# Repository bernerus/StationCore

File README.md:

View this project on [CADLAB.io](https://cadlab.io/project/27342). 

# StationCore

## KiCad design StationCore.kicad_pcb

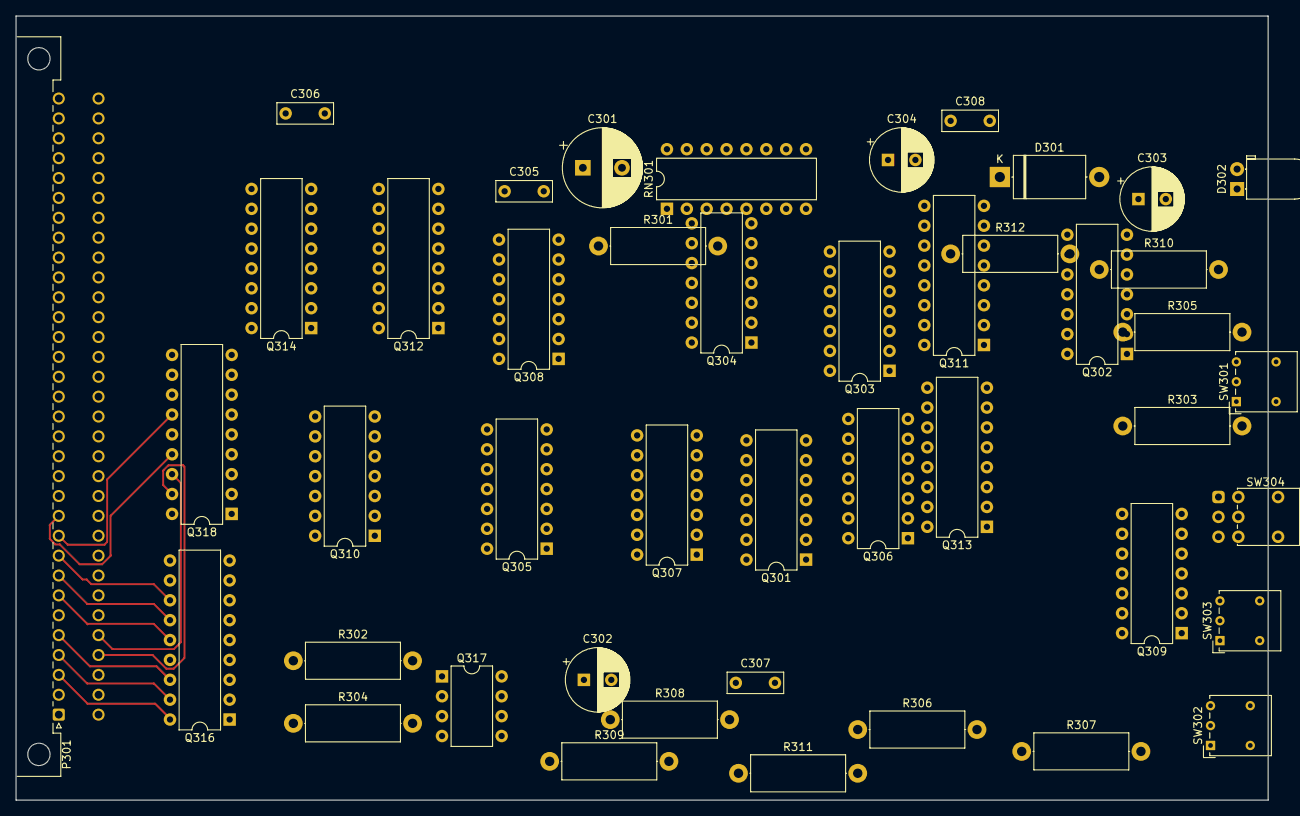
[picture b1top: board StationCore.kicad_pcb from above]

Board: 2 copper layers, 160.0 x 100.2 mm, 45 parts (0 on the bottom side), 69 nets.

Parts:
C301: 100μF; CP_Radial_D10.0mm_P5.00mm
C302: 10μF; CP_Radial_D8.0mm_P3.50mm
C303: 39μF; CP_Radial_D8.0mm_P3.50mm
C304: 22μF; CP_Radial_D8.0mm_P3.50mm
C305, C306, C307, C308: 47n; C_Rect_L7.0mm_W2.5mm_P5.00mm
D301: BZX74C4v2; D_DO-201AE_P12.70mm_Horizontal
D302: PA RDY; LED_D5.0mm_Horizontal_O1.27mm_Z3.0mm
P301: DIN2; DIN41612_C_2x32_Male_Horizontal_THT
Q301: 7402; DIP-14_W7.62mm
Q302: 74LS32; DIP-14_W7.62mm
Q303, Q309: 74LS08; DIP-14_W7.62mm
Q304: 74HCT04; DIP-14_W7.62mm
Q305: 74HC74; DIP-14_W7.62mm
Q306, Q307: 74LS00; DIP-14_W7.62mm
Q308: 74HC14; DIP-14_W7.62mm
Q310: 74LS21; DIP-14_W7.62mm
Q311, Q313: 74LS123; DIP-16_W7.62mm
Q312, Q314: PCF8574; DIP-16_W7.62mm
Q316, Q318: ULN2803A; DIP-18_W7.62mm
Q317: 82B715; DIP-8_W7.62mm
R301: 470k; R_Axial_DIN0414_L11.9mm_D4.5mm_P15.24mm_Horizontal
R302, R303: 39k; R_Axial_DIN0414_L11.9mm_D4.5mm_P15.24mm_Horizontal
R304, R305, R306: 22k; R_Axial_DIN0414_L11.9mm_D4.5mm_P15.24mm_Horizontal
R307, R311, R312: 27k; R_Axial_DIN0414_L11.9mm_D4.5mm_P15.24mm_Horizontal
R308, R309: 680; R_Axial_DIN0414_L11.9mm_D4.5mm_P15.24mm_Horizontal
R310: 279; R_Axial_DIN0414_L11.9mm_D4.5mm_P15.24mm_Horizontal
RN301: 4k7; DIP-16_W7.62mm
SW301: XRX_432; SW_Lever_1P2T_NKK_GW12LxH
SW302: QRO; SW_Lever_1P2T_NKK_GW12LxH
SW303: xxx; SW_Lever_1P2T_NKK_GW12LxH
SW304: PA_OFF; SW_Push_2P2T_Vertical_E-Switch_800UDP8P1A1M6

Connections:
432_L: P301.a6, Q301.6, Q304.1, Q305.3 (C), Q306.13, Q307.5, Q312.12 (P7), RN301.8 (R8)
432_RX: Q309.6, Q316.4 (I4)
432_RX_PWR_EN: Q301.13, Q316.3 (I3)
432_RX_PWR_EN_L: P301.a5, Q316.16 (O3)
432_TX_PWR_EN: Q301.3, Q301.4, Q304.13, Q316.1 (I1)
432_TX_PWR_EN_L: P301.a3, Q304.12, Q307.12, Q309.5, Q316.18 (O1)
GND: C305.2, C306.2, C307.2, C308.2, D301.2 (A), P301.a26, P301.c26, Q301.7 (GND), Q302.7 (GND), Q302.9, Q303.7 (GND), Q304.7 (GND), Q305.7 (GND), Q305.11 (C), Q305.12 (D), Q306.7 (GND), Q307.7 (GND), Q308.7 (GND), Q309.7 (GND), Q310.7 (GND), Q311.8 (GND), Q311.9 (A), Q312.1 (A0), Q312.8 (VSS), Q313.1 (A), Q313.8 (GND), Q313.9 (A), Q314.8 (VSS), Q316.9 (GND), Q317.4 (GND), Q318.9 (GND), R306.1, R307.2, R311.2, R312.2, SW301.2 (B), SW302.2 (B), SW303.2 (B), SW304.1
unnamed: D302.2 (A), R310.2
unnamed: P301.a7, Q316.14 (O5)
unnamed: P301.a28, P301.c28, Q316.10 (COM), Q318.10 (COM)
unnamed: P301.c1, Q317.7 (LCL), R309.2
unnamed: P301.c2, Q317.2 (LDA), R308.2
unnamed: Q301.1, Q301.11, Q301.12
unnamed: Q302.6, Q309.12
unnamed: Q303.1, Q308.10
unnamed: Q303.11, Q304.11
unnamed: Q304.5, Q308.6
unnamed: Q305.1 (~R), Q307.6
unnamed: Q305.4 (~S), Q306.11
unnamed: Q305.10 (~S), RN301.4 (R4), SW302.1 (A)
unnamed: Q307.3, Q307.4
unnamed: C301.2, Q311.14 (Cext)
unnamed: C301.1, Q311.15 (RCext), R301.1
unnamed: Q309.8, Q311.10 (B)
unnamed: C302.2, Q311.6 (Cext)
unnamed: C302.1, Q311.7 (RCext), R302.2
unnamed: Q308.8, Q312.4 (P0)
unnamed: Q312.9 (P4), Q314.9 (P4)
unnamed: Q312.14 (SCL), Q314.14 (SCL), Q317.6 (SCL), R304.2
unnamed: Q312.15 (SDA), Q314.15 (SDA), Q317.3 (SDA), R305.2
unnamed: C303.2, Q313.14 (Cext)
unnamed: C303.1, Q313.15 (RCext), R303.2
unnamed: Q310.4, Q313.4 (~Q)
unnamed: C304.2, Q313.6 (Cext)
unnamed: Q313.11 (Clr), RN301.6 (R6)
unnamed: C304.1, Q313.7 (RCext), RN301.7 (R7)
PA Remote ON: Q305.13 (~R), Q312.6 (P2), Q314.6 (P2), RN301.12 (R12), SW302.3 (C)
PA Remote off: Q309.13, Q314.4 (P0), RN301.5 (R5), SW304.2
PA_ACTIVE: C308.1, P301.c22, Q308.9, R312.1
PA_KEEPALIVE: Q302.4, Q311.13 (Q)
PA_OFF: Q309.11, Q318.3 (I3)
PA_OFF_L: P301.c5, Q318.16 (O3)
PA_ON: Q311.5 (Q), Q316.8 (I8)
PA_ON_L: P301.c3, Q316.11 (O8)
PA_PASS_THRU: P301.a10, Q318.13 (O6)
PA_READY: C305.1, D301.1 (K), P301.c8, Q304.6, Q308.5, Q309.2, Q312.5 (P1), Q318.5 (I5), R306.2
PA_READY_L: D302.1 (K), Q318.14 (O5)
PA_UNBIAS: Q310.6, Q318.2 (I2)
PA_UNBIAS_L: P301.c4, Q318.17 (O2)
PREAMP_DISABLE_1_L: Q310.13, Q313.12 (~Q)
PREAMP_DISABLE_2_L: Q308.12, Q310.9, Q313.10 (B)
PREAMP_EN: Q310.8, Q318.4 (I4)
PREAMP_EN_L: P301.a11, Q318.15 (O4)
QRO_ACTIVE: Q305.2 (D), Q305.5 (Q), Q306.12, Q307.1, Q307.2, Q309.3, Q310.2, Q318.1 (I1), Q318.6 (I6)
QRO_EN: Q305.8 (~Q), Q309.1, Q309.9
RIG_ACTIVE: Q302.3, Q302.5, Q303.12, Q309.10, Q311.1 (A)
RX_144_EN_L: Q307.11, Q308.13
RX_432_EN: Q301.2, Q302.8, Q309.4
RX_432_L: Q308.11, RN301.1 (R1), SW303.3 (C)
TRX_RX_EN: C307.1, P301.c30, Q302.2, Q303.2, Q304.4, Q307.13, Q308.3, Q316.6 (I6), R311.1
TRX_RX_EN_L: Q304.3, Q308.4, Q312.11 (P6)
TRX_TX_432: Q304.10, Q316.7 (I7)
TRX_TX_432_L: P301.a9, Q316.12 (O7)
TRX_TX_EN: C306.1, P301.a30, Q302.1, Q303.10, Q304.2, Q308.1, Q310.5, Q313.2 (B), R307.1
TRX_TX_EN_L: Q301.5, Q303.13, Q308.2, Q312.10 (P5), Q314.10 (P5), RN301.2 (R2)
VCC: P301.a24, P301.c24, Q301.14 (VCC), Q302.14 (VCC), Q303.14 (VCC), Q304.14 (VCC), Q305.14 (VCC), Q306.14 (VCC), Q307.14 (VCC), Q308.14 (VCC), Q309.14 (VCC), Q310.14 (VCC), Q311.2 (B), Q311.16 (VCC), Q312.2 (A1), Q312.3 (A2), Q312.16 (VDD), Q313.16 (VCC), Q314.1 (A0), Q314.2 (A1), Q314.3 (A2), Q314.16 (VDD), Q317.8 (VCC), R301.2, R302.1, R303.1, R304.1, R305.1, R308.1, R309.1, R310.1, RN301.16 (common)
XCVR_RX_432: Q302.10, Q303.3, Q316.2 (I2)
XCVR_RX_432_L: P301.a4, Q316.17 (O2)
XCVR_RX_L: P301.a8, Q316.13 (O6)

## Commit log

2023-09-17 Added .gitignore file
2023-09-17 Backlink to CADLAB.io has been added.
